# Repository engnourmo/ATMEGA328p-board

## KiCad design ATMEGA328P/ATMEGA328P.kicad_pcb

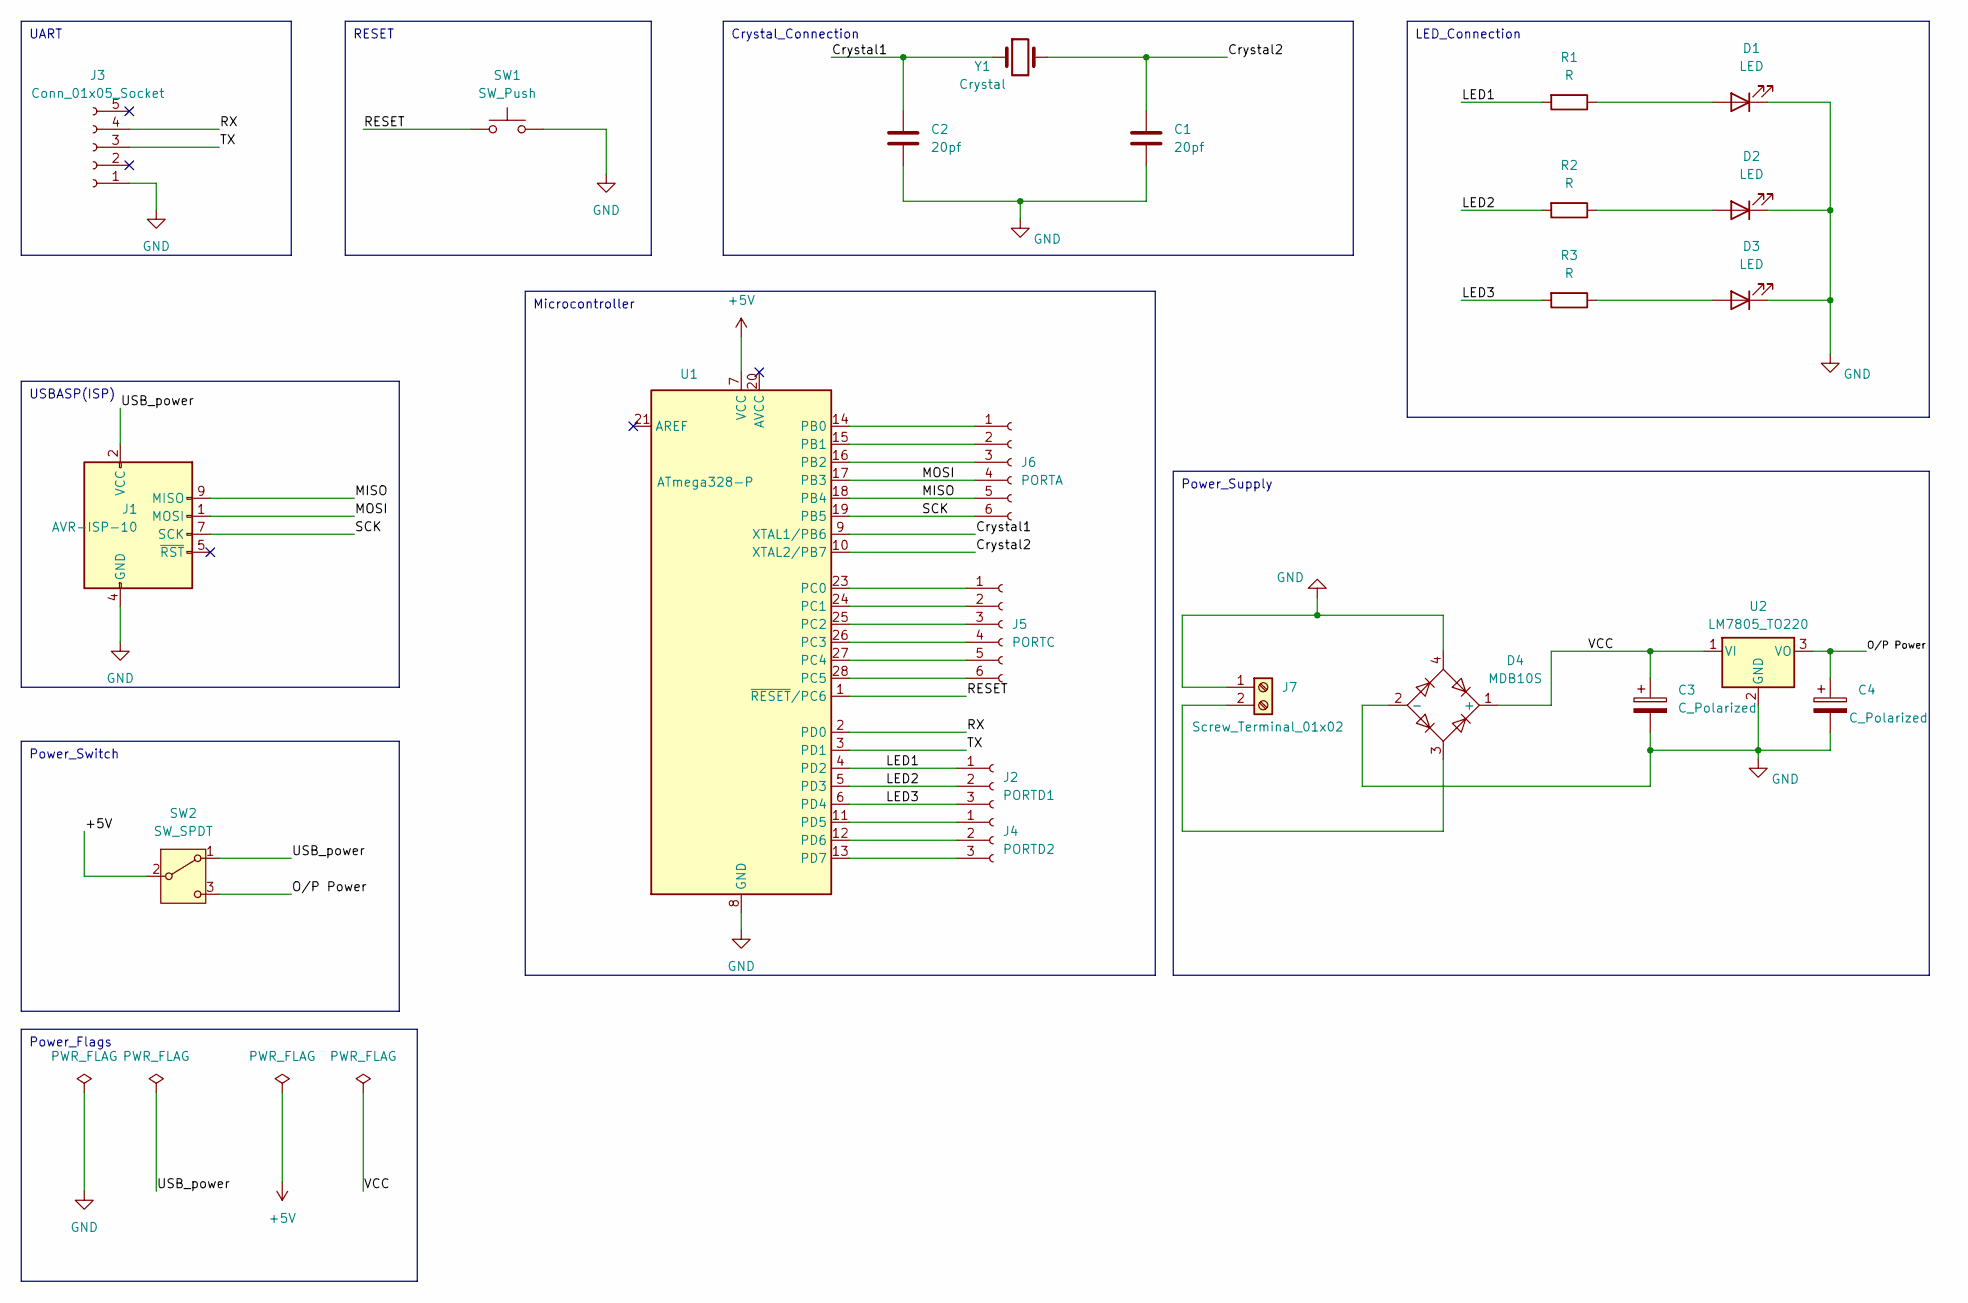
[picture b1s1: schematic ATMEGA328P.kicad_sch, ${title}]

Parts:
C1, C2: 20pf; C_Disc_D3.0mm_W1.6mm_P2.50mm
C3, C4: C_Polarized; CP_Axial_L10.0mm_D4.5mm_P15.00mm_Horizontal
D1, D2, D3: LED; LED_D8.0mm
D4: MDB10S; TSSOP-4_4.4x5mm_P4mm
J1: AVR-ISP-10; IDC-Header_2x05_P2.54mm_Horizontal
J2: PORTD1; PinSocket_1x03_P1.00mm_Vertical
J3: Conn_01x05_Socket; PinSocket_1x05_P1.00mm_Vertical
J4: PORTD2; PinSocket_1x03_P1.00mm_Vertical
J5: PORTC; PinSocket_1x06_P1.00mm_Vertical
J6: PORTA; PinSocket_1x06_P1.00mm_Vertical
J7: Screw_Terminal_01x02; TerminalBlock_Phoenix_MKDS-3-2-5.08_1x02_P5.08mm_Horizontal
R1, R2, R3: R; R_Axial_DIN0204_L3.6mm_D1.6mm_P5.08mm_Horizontal
SW1: SW_Push; SW_PUSH_6mm_H4.3mm
SW2: SW_SPDT; SW_MINI-SPDT-SW
U1: ATmega328-P; DIP-28_W7.62mm
U2: LM7805_TO220; TO-220-3_Vertical
Y1: Crystal; Crystal_HC49-4H_Vertical

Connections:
+5V: SW2.2 (B), U1.7 (VCC)
/Crystal1: C2.1, U1.9 (XTAL1/PB6), Y1.1
/Crystal2: C1.1, U1.10 (XTAL2/PB7), Y1.2
/LED1: J2.1, R1.2, U1.4 (PD2)
/LED2: J2.2, R2.2, U1.5 (PD3)
/LED3: J2.3, R3.2, U1.6 (PD4)
/MISO: J1.9 (MISO), J6.5, U1.18 (PB4)
/MOSI: J1.1 (MOSI), J6.4, U1.17 (PB3)
/O/P Power: C4.1, SW2.3 (C), U2.3 (VO)
/RESET: SW1.1, U1.1 (~RESET/PC6)
/RX: J3.4, U1.2 (PD0)
/SCK: J1.7 (SCK), J6.6, U1.19 (PB5)
/TX: J3.3, U1.3 (PD1)
/USB_power: J1.2 (VCC), SW2.1 (A)
/VCC: C3.1, D4.1 (+), U2.1 (VI)
GND: C1.2, C2.2, C3.2, C4.2, D1.1 (K), D2.1 (K), D3.1 (K), D4.2 (-), D4.4, J1.4 (GND), J1.6 (GND), J1.8 (GND), J1.10 (GND), J3.1, J7.1, SW1.2, U1.8 (GND), U1.22 (GND), U2.2 (GND)
unnamed: D1.2 (A), R1.1
unnamed: D2.2 (A), R2.1
unnamed: D3.2 (A), R3.1
unnamed: J4.1, U1.11 (PD5)
unnamed: J4.2, U1.12 (PD6)
unnamed: J4.3, U1.13 (PD7)
unnamed: J5.1, U1.23 (PC0)
unnamed: J5.2, U1.24 (PC1)
unnamed: J5.3, U1.25 (PC2)
unnamed: J5.4, U1.26 (PC3)
unnamed: J5.5, U1.27 (PC4)
unnamed: J5.6, U1.28 (PC5)
unnamed: J6.1, U1.14 (PB0)
unnamed: J6.2, U1.15 (PB1)
unnamed: J6.3, U1.16 (PB2)
unnamed: D4.3, J7.2

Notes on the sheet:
Power_Switch
RESET
Power_Flags
LED_Connection
USBASP(ISP)
Power_Supply
Microcontroller
UART
Crystal_Connection

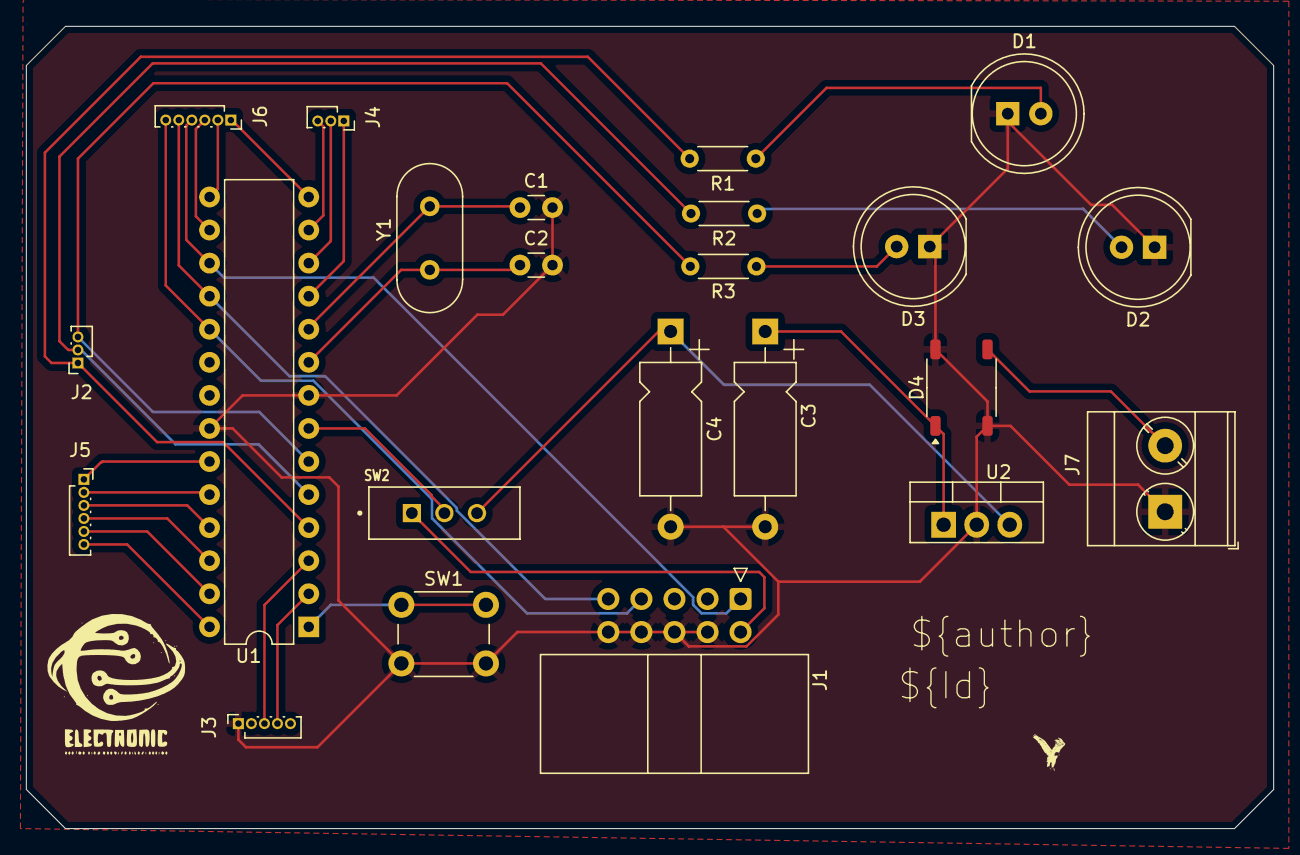
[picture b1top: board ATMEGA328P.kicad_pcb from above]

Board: 2 copper layers, 95.8 x 61.6 mm, 23 parts (0 on the bottom side), 32 nets.

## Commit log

2025-03-16 added project file
2025-03-16 added schematic PDF
